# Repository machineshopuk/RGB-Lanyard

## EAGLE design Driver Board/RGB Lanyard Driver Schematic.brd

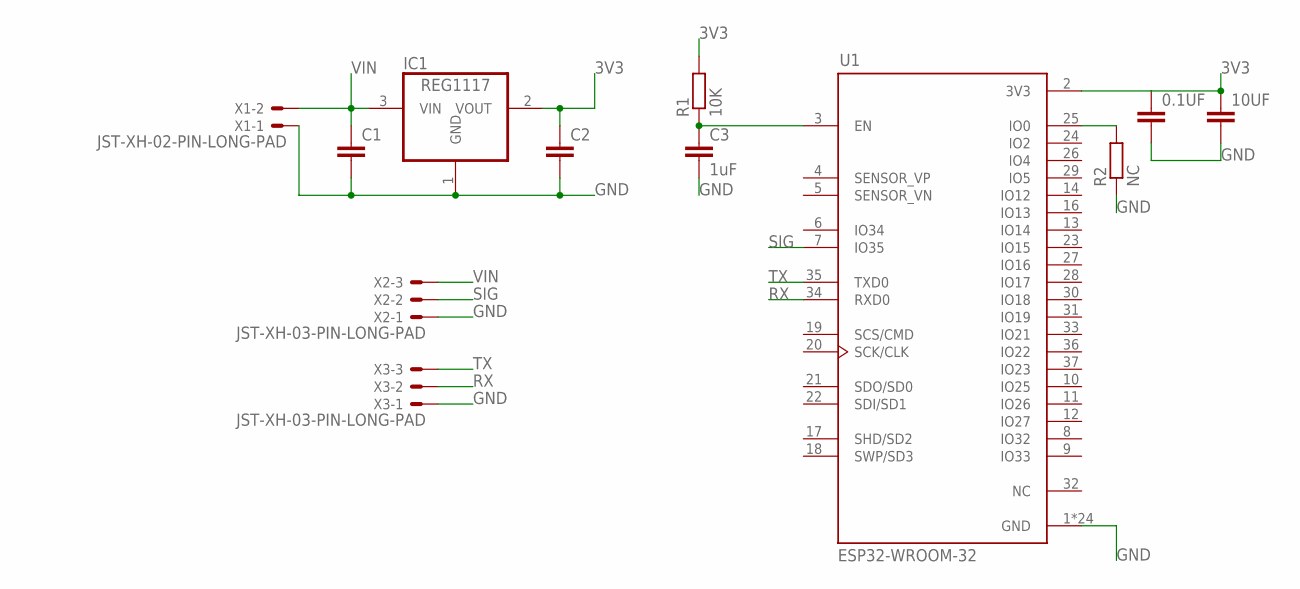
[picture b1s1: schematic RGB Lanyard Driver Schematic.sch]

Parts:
0.1UF, 10UF: C-EUC0805; C0805
C1, C2: C-EUC0805; C0805
C3: 1uF; C0805
IC1: REG1117; SOT223
R1: 10K; R0805
R2: NC; R0805
U1: ESP32-WROOM-32; MODULE_ESP32-WROOM-32
X1: JST-XH-02-PIN-LONG-PAD; JST-XH-02-PACKAGE-LONG-PAD
X2, X3: JST-XH-03-PIN-LONG-PAD; JST-XH-03-PACKAGE-LONG-PAD

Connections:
3V3: 0.1UF.1, 10UF.1, C2.1, IC1.2 (VOUT), R1.2, U1.2 (3V3)
GND: 0.1UF.2, 10UF.2, C1.2, C2.2, C3.2, IC1.1 (GND), R2.1, U1.1 (GND), U1.15 (GND), U1.38 (GND), U1.39_1 (GND), U1.39_2 (GND), U1.39_3 (GND), U1.39_4 (GND), U1.39_5 (GND), U1.39_6 (GND), U1.39_7 (GND), U1.39_8 (GND), U1.39_9 (GND), U1.39_10 (GND), U1.39_11 (GND), U1.39_12 (GND), U1.39_13 (GND), U1.39_14 (GND), U1.39_15 (GND), U1.39_16 (GND), U1.39_17 (GND), U1.39_18 (GND), U1.39_19 (GND), U1.39_20 (GND), U1.39_21 (GND), X1.1, X2.1, X3.1
unnamed: C3.1, R1.1, U1.3 (EN)
unnamed: R2.2, U1.25 (IO0)
RX: U1.34 (RXD0), X3.2
SIG: U1.7 (IO35), X2.2
TX: U1.35 (TXD0), X3.3
VIN: C1.1, IC1.3 (VIN), X1.2, X2.3

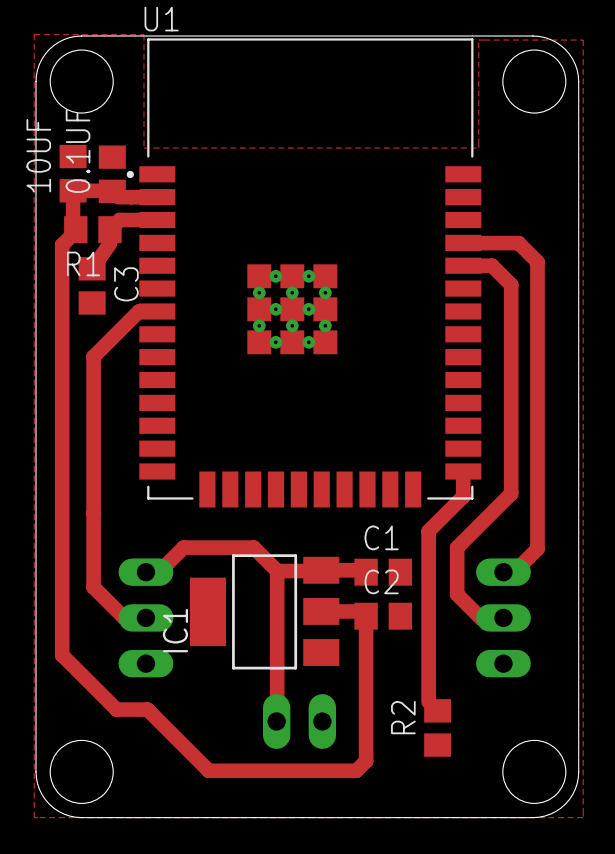
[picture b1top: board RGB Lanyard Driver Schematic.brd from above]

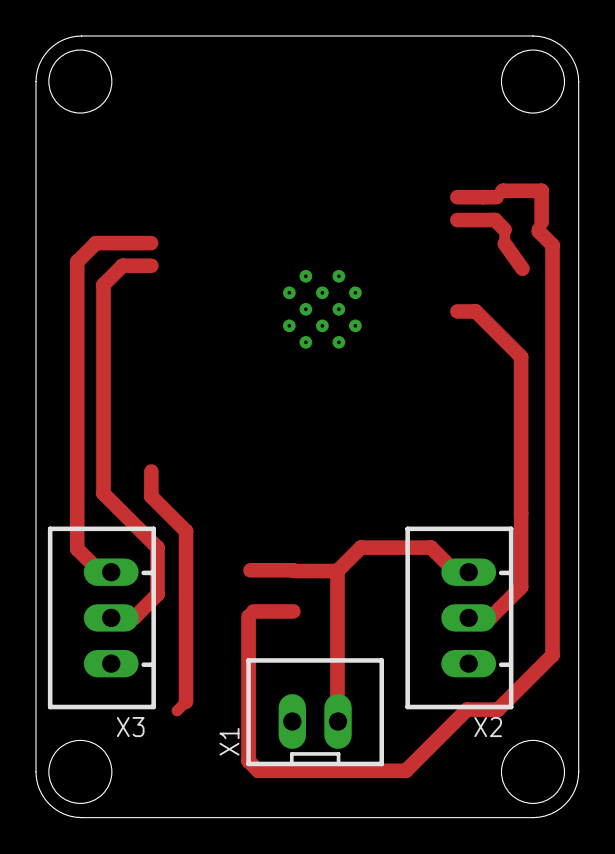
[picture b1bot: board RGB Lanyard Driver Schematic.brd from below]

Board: 2 copper layers, 30.1 x 43.4 mm, 12 parts (3 on the bottom side), 8 nets.
